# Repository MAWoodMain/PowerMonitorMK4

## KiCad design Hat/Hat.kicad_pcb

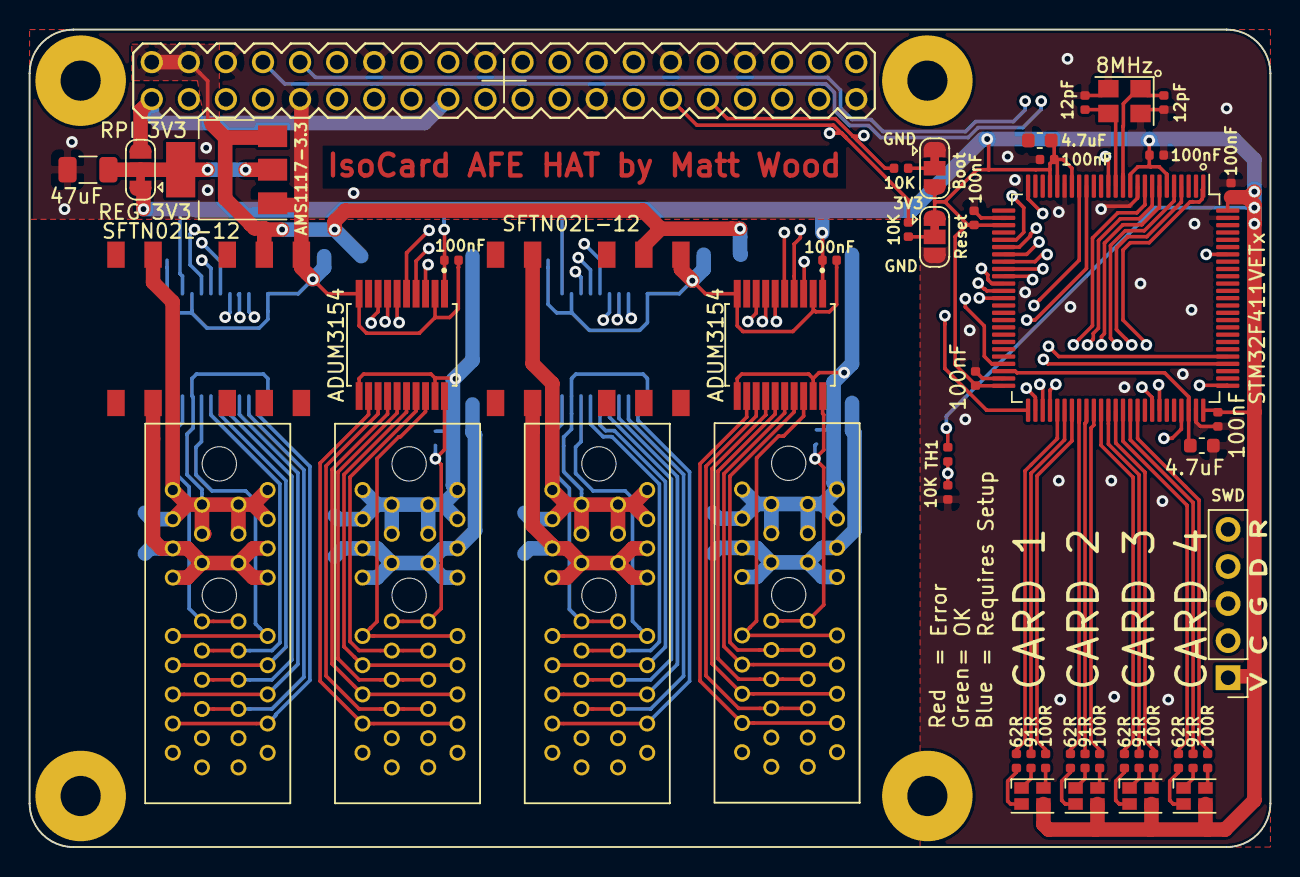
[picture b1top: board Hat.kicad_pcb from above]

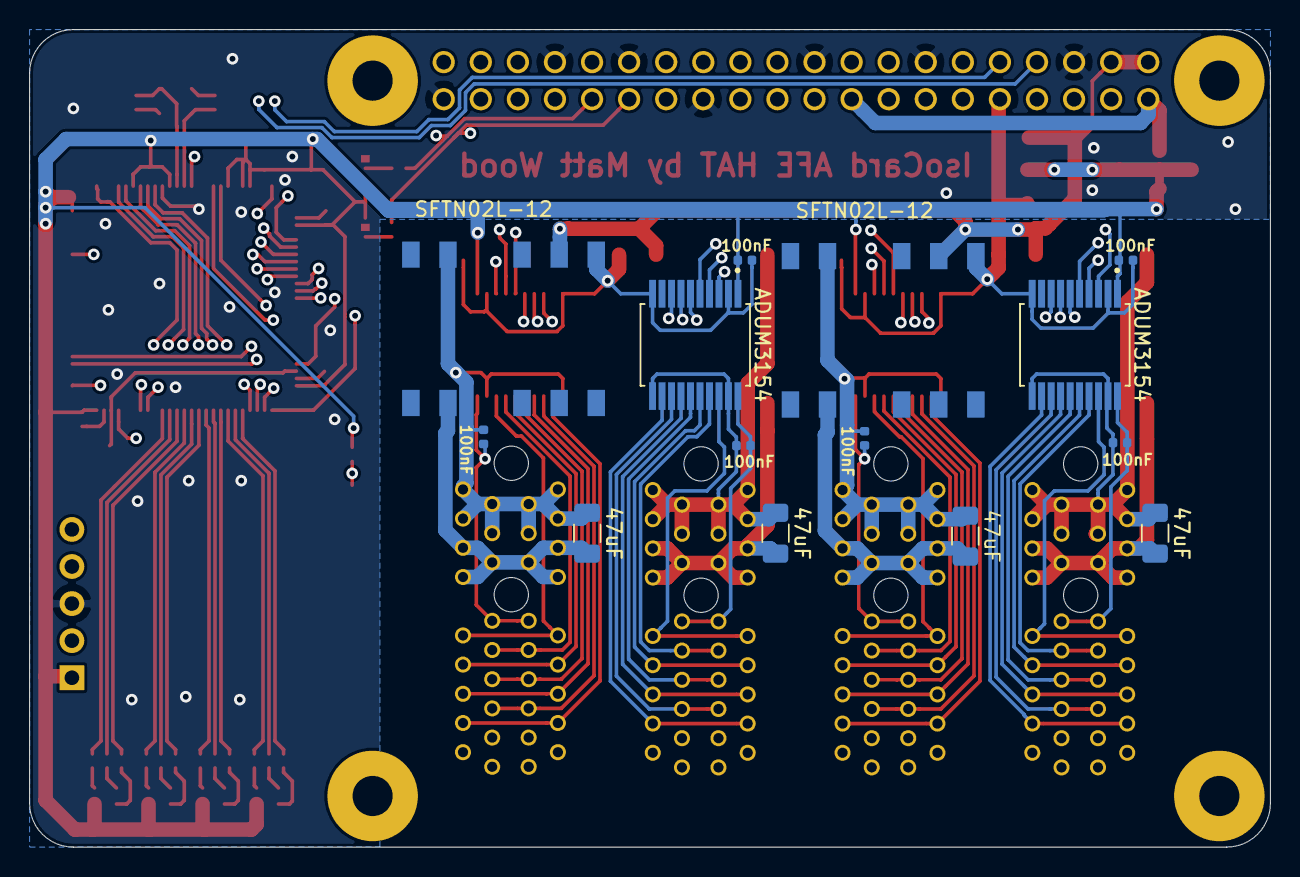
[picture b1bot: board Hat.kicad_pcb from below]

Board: 4 copper layers, 85.0 x 56.0 mm, 63 parts (14 on the bottom side), 105 nets.

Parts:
C1, C2: 4.7uF; C_0603_1608Metric
C3, C4, C5, C6, C7, C8, C11, C12, C13, C14, C15, C16, C17, C18: 100nF; C_0402_1005Metric
C9, C10: 12pF; C_0402_1005Metric
C19, C20, C21, C22, C23: 47uF; C_1206_3216Metric
CRD1, CRD2, CRD3, CRD4: AFE_Card_Interface; PCIE-036-02-X-D-TH
D1, D2, D3, D4: LED_RBAG; LED_Cree-PLCC4_2x2mm_CW
J1: Raspberry_Pi_2_3; RASPBERRY_PI_B+
J2: SWD; PinHeader_1x05_P2.54mm_Vertical
JP1: Reset; SolderJumper-3_P1.3mm_Bridged12_RoundedPad1.0x1.5mm
JP2: Boot; SolderJumper-3_P1.3mm_Bridged12_RoundedPad1.0x1.5mm
JP3: 3V3 SEL; SolderJumper-3_P1.3mm_Bridged12_RoundedPad1.0x1.5mm
PS1, PS2, PS3, PS4: SFTN02L-12; SFTN02
R1, R2: 10K; R_0402_SILK_VAL
R3, R4, R5, R6: 91R; R_0402_SILK_VAL
R7, R8, R9, R10: 62R; R_0402_SILK_VAL
R11, R12, R13, R14: 100R; R_0402_SILK_VAL
R15: 10K; R_0402_1005Metric
TH1: 10K; R_0402_1005Metric
U1, U2, U3, U4: ADUM3154; SOP65P780X200-20N
U5: STM32F411VETx; LQFP-100_14x14mm_P0.5mm
U6: AMS1117-3.3; SOT-223-3_TabPin2
Y1: 8MHz; Crystal_SMD_3225-4Pin_3.2x2.5mm

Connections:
+3.3VP: J1.1, J1.17, JP3.3
+3V3: C2.1, C3.1, C4.1, C5.1, C6.1, C7.1, C8.1, C11.1, C12.1, C13.1, C14.1, D1.3, D2.3, D3.3, D4.3, J2.1, JP1.1, JP2.3, JP3.1, TH1.1, U1.1, U2.1, U3.1, U4.1, U5.6, U5.11, U5.19, U5.21, U5.22, U5.28, U5.50, U5.75, U5.100
+5V: J1.2, J1.4, PS1.2, PS2.2, PS3.2, PS4.2, U6.3
/B1: D1.2, R11.1
/B1IO: R11.2, U5.57
/B2: D2.2, R12.1
/B2IO: R12.2, U5.60
/B3: D3.2, R13.1
/B3IO: R13.2, U5.63
/B4: D4.2, R14.1
/B4IO: R14.2, U5.66
/Board_Temp: R15.1, TH1.2, U5.25
/G1: D1.4, R7.1
/G1IO: R7.2, U5.55
/G2: D2.4, R8.1
/G2IO: R8.2, U5.58
/G3: D3.4, R9.1
/G3IO: R9.2, U5.61
/G4: D4.4, R10.1
/G4IO: R10.2, U5.64
/R1: D1.1, R3.1
/R1IO: R3.2, U5.56
/R2: D2.1, R4.1
/R2IO: R4.2, U5.59
/R3: D3.1, R5.1
/R3IO: R5.2, U5.62
/R4: D4.1, R6.1
/R4IO: R6.2, U5.65
/SPI1_MISO: U1.5, U5.31
/SPI1_MOSI: U1.4, U5.32
/SPI1_SCK: U1.3, U5.30
/SPI2_MISO: U2.5, U5.17
/SPI2_MOSI: U2.4, U5.18
/SPI2_SCK: U2.3, U5.47
/SPI3_MISO: U3.5, U5.79
/SPI3_MOSI: U3.4, U5.80
/SPI3_SCK: U3.3, U5.51
/SPI4_MISO: U4.5, U5.4
/SPI4_MOSI: U4.4, U5.5
/SPI4_SCK: U4.3, U5.1
/SSA1: U1.6, U5.33
/SSA2: U2.6, U5.38
/SSA3: U3.6, U5.52
/SSA4: U4.6, U5.7
/SSB1: U1.7, U5.34
/SSB2: U2.7, U5.37
/SSB3: U3.7, U5.53
/SSB4: U4.7, U5.8
/SSC1: U1.8, U5.35
/SSC2: U2.8, U5.36
/SSC3: U3.8, U5.54
/SSC4: U4.8, U5.9
/ST_BOOT0: J1.31, R2.2, U5.94
/ST_RST: J1.29, J2.5, R1.2, U5.14
/SWCLK: J2.2, U5.76
/SWDIO: J2.4, U5.72
/USART1_RX: J1.8, U5.69
/USART1_TX: J1.10, U5.68
/XTAL_IN: C9.1, U5.12, Y1.1
/XTAL_OUT: C10.1, U5.13, Y1.3
GND: C1.2, C2.2, C3.2, C4.2, C5.2, C6.2, C7.2, C8.2, C9.2, C10.2, C11.2, C12.2, C13.2, C14.2, C23.2, J1.6, J1.9, J1.14, J1.20, J1.25, J1.30, J1.34, J1.39, J2.3, JP1.3, JP2.1, PS1.1, PS2.1, PS3.1, PS4.1, R15.2, U1.2, U1.10, U2.2, U2.10, U3.2, U3.10, U4.2, U4.10, U5.10, U5.20, U5.27, U5.49, U5.74, U5.99, U6.1, Y1.2, Y1.4
unnamed: C1.1, U5.48, U5.73
unnamed: C15.1, C19.2, CRD1.A15, CRD1.A16, CRD1.A17, CRD1.A18, CRD1.B15, CRD1.B16, CRD1.B17, CRD1.B18, PS1.5, U1.11, U1.19
unnamed: C15.2, CRD1.A11, CRD1.B11, U1.20
unnamed: C16.1, C20.2, CRD2.A15, CRD2.A16, CRD2.A17, CRD2.A18, CRD2.B15, CRD2.B16, CRD2.B17, CRD2.B18, PS2.5, U2.11, U2.19
unnamed: C16.2, CRD2.A11, CRD2.B11, U2.20
unnamed: C17.1, C21.2, CRD3.A15, CRD3.A16, CRD3.A17, CRD3.A18, CRD3.B15, CRD3.B16, CRD3.B17, CRD3.B18, PS3.5, U3.11, U3.19
unnamed: C17.2, CRD3.A11, CRD3.B11, U3.20
unnamed: C18.1, C22.2, CRD4.A15, CRD4.A16, CRD4.A17, CRD4.A18, CRD4.B15, CRD4.B16, CRD4.B17, CRD4.B18, PS4.5, U4.11, U4.19
unnamed: C18.2, CRD4.A11, CRD4.B11, U4.20
unnamed: C19.1, CRD1.A12, CRD1.A13, CRD1.A14, CRD1.B12, CRD1.B13, CRD1.B14, PS1.8
unnamed: C20.1, CRD2.A12, CRD2.A13, CRD2.A14, CRD2.B12, CRD2.B13, CRD2.B14, PS2.8
unnamed: C21.1, CRD3.A12, CRD3.A13, CRD3.A14, CRD3.B12, CRD3.B13, CRD3.B14, PS3.8
unnamed: C22.1, CRD4.A12, CRD4.A13, CRD4.A14, CRD4.B12, CRD4.B13, CRD4.B14, PS4.8
unnamed: C23.1, JP3.2, U6.2
unnamed: CRD1.A4, CRD1.B4, U1.12
unnamed: CRD1.A5, CRD1.B5, U1.13
unnamed: CRD1.A6, CRD1.B6, U1.14
unnamed: CRD1.A7, CRD1.B7, U1.15
unnamed: CRD1.A8, CRD1.B8, U1.16
unnamed: CRD1.A9, CRD1.B9, U1.17
unnamed: CRD1.A10, CRD1.B10, U1.18
unnamed: CRD2.A4, CRD2.B4, U2.12
unnamed: CRD2.A5, CRD2.B5, U2.13
unnamed: CRD2.A6, CRD2.B6, U2.14
unnamed: CRD2.A7, CRD2.B7, U2.15
unnamed: CRD2.A8, CRD2.B8, U2.16
unnamed: CRD2.A9, CRD2.B9, U2.17
unnamed: CRD2.A10, CRD2.B10, U2.18
unnamed: CRD3.A4, CRD3.B4, U3.12
unnamed: CRD3.A5, CRD3.B5, U3.13
unnamed: CRD3.A6, CRD3.B6, U3.14
unnamed: CRD3.A7, CRD3.B7, U3.15
unnamed: CRD3.A8, CRD3.B8, U3.16
unnamed: CRD3.A9, CRD3.B9, U3.17
unnamed: CRD3.A10, CRD3.B10, U3.18
unnamed: CRD4.A4, CRD4.B4, U4.12
unnamed: CRD4.A5, CRD4.B5, U4.13
unnamed: CRD4.A6, CRD4.B6, U4.14
unnamed: CRD4.A7, CRD4.B7, U4.15
unnamed: CRD4.A8, CRD4.B8, U4.16
unnamed: CRD4.A9, CRD4.B9, U4.17
unnamed: CRD4.A10, CRD4.B10, U4.18
unnamed: JP1.2, R1.1
unnamed: JP2.2, R2.1

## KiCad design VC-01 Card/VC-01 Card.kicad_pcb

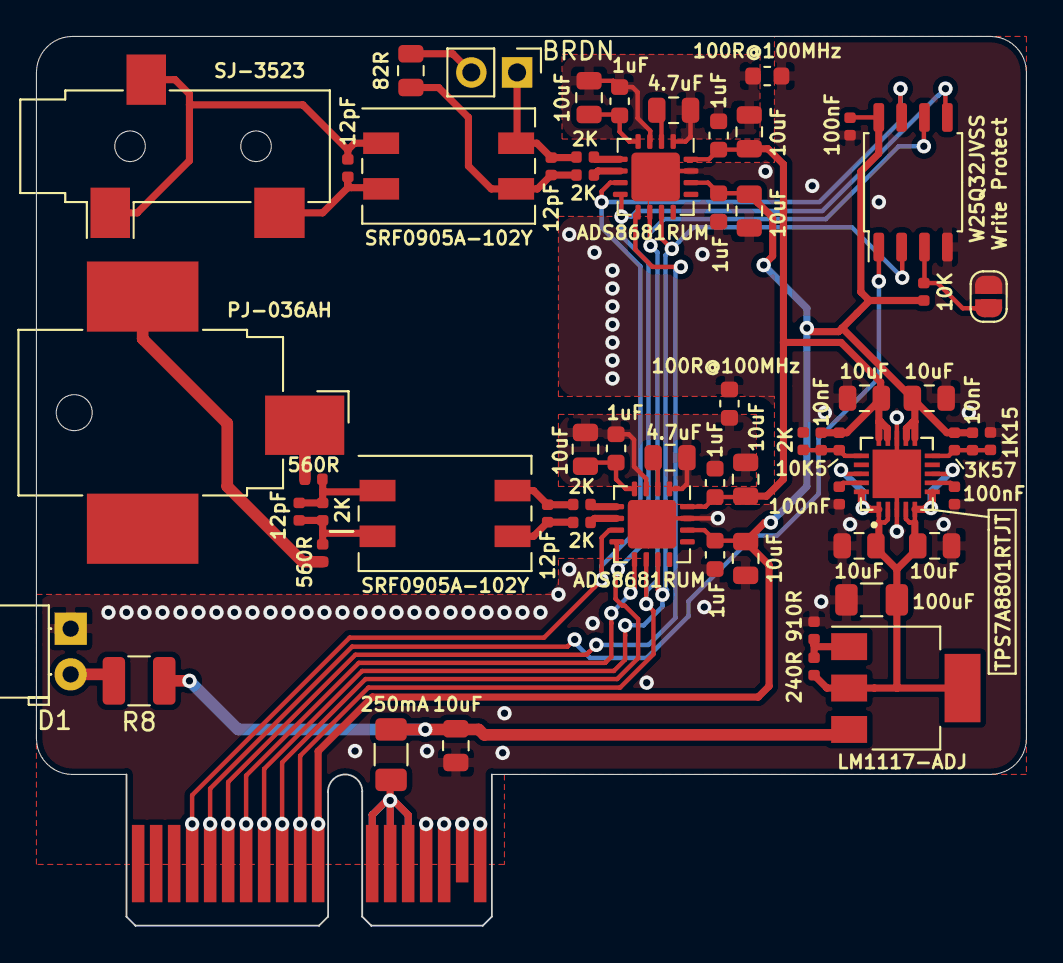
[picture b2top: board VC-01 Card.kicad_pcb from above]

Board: 2 copper layers, 55.0 x 49.4 mm, 61 parts (0 on the bottom side), 41 nets.

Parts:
C1, C2, C7, C8: 12pF; C_0402_1005Metric
C3, C4, C12, C13, C16, C17, C22, C23, C26, C27, C29: 10uF; C_0805_2012Metric
C5, C6, C9: 100nF; C_0402_1005Metric
C10, C11, C18, C19, C20, C21: 1uF; C_0603_1608Metric
C14, C15: 4.7uF; C_0805_2012Metric
C24, C25: 10nF; C_0402_1005Metric
C28: 100uF; C_1206_3216Metric
CRD1: AFE_Card_Interface; BUS_PCIexpress_x1
D1: LED; LED_D5.0mm_Horizontal_O1.27mm_Z3.0mm
F1: 250mA; Fuse_1206_3216Metric
FB1, FB2: 100R@100MHz; R_0603_1608Metric
FL1, FL2: SRF0905A-102Y; Filter_Bourns_SRF0905_6.0x9.2mm
J1: SJ-3523; Jack_3.5mm_CUI_SJ-3523-SMT_Horizontal
J2: PJ-036AH; BarrelJack_CUI_PJ-036AH-SMT_Horizontal
J3: BRDN; PinHeader_1x02_P2.54mm_Vertical
JP1: Write Protect; SolderJumper-2_P1.3mm_Open_RoundedPad1.0x1.5mm
R1: 82R; R_0805_2012Metric
R2, R3, R6, R11, R12, R13: 2K; R_0402_1005Metric
R4: 10K5; R_0402_1005Metric
R5: 3K57; R_0402_1005Metric
R7: 1K15; R_0402_1005Metric
R8: R; R_1210_3225Metric
R9, R10: 560R; R_0402_1005Metric
R14: 10K; R_0402_1005Metric
R15: 240R; R_0402_1005Metric
R16: 910R; R_0402_1005Metric
U1, U3: ADS8681RUM; QFN-16-1EP_4x4mm_P0.65mm_EP2.7x2.7mm
U2: TPS7A8801RTJT; QFN50P400X400X80-21N
U4: W25Q32JVSS; SOIC-8_5.23x5.23mm_P1.27mm
U5: LM1117-ADJ; SOT-223-3_TabPin2

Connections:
+3V3: C3.1, C9.2, C20.1, C21.1, C22.1, C23.1, C25.2, CRD1.A11, CRD1.B11, R5.1, R14.1, U1.14, U2.11, U2.12, U3.14, U4.8
+5V: C4.1, C10.1, C11.1, C12.1, C13.1, C24.2, R4.1, U1.16, U2.14, U2.15, U3.16
+12V: C29.1, F1.2, R8.1, U5.3
/SCLK: CRD1.A10, CRD1.B10, U1.10, U3.10, U4.6
/SI: CRD1.A9, CRD1.B9, U1.8, U3.8, U4.5
/SO: CRD1.A8, CRD1.B8, U1.11, U3.11, U4.2
/U1_GNDA: C11.2, C13.2, C15.2, C17.2, C19.2, FB1.1, U1.1, U1.3
/U3_GNDA: C10.2, C12.2, C14.2, C16.2, C18.2, FB2.1, U3.1, U3.3
/~CS_CURRENT: CRD1.A6, CRD1.B6, U1.9
/~CS_FLASH: CRD1.A5, CRD1.B5, U4.1
/~CS_VOLTAGE: CRD1.A7, CRD1.B7, U3.9
/~RST: CRD1.A4, CRD1.B4, U1.7, U3.7, U4.7
GND: C3.2, C4.2, C5.1, C6.1, C9.1, C20.2, C21.2, C22.2, C23.2, C26.2, C27.2, C28.2, C29.2, CRD1.A15, CRD1.A16, CRD1.A17, CRD1.A18, CRD1.B15, CRD1.B16, CRD1.B17, CRD1.B18, D1.1, FB1.2, FB2.2, JP1.2, R6.2, R7.2, R16.2, U1.15, U1.17, U2.3, U2.13, U2.21, U3.15, U3.17, U4.4
unnamed: C1.1, FL1.1, J1.R, J1.S
unnamed: C1.2, FL1.2, J1.T
unnamed: C2.1, FL1.4, J3.1, R2.2
unnamed: C2.2, FL1.3, R1.2, R3.2
unnamed: C5.2, U2.19
unnamed: C6.2, U2.7
unnamed: C7.1, FL2.1, R10.1, R11.1
unnamed: C7.2, FL2.2, R9.1, R11.2
unnamed: C8.1, FL2.4, R12.2
unnamed: C8.2, FL2.3, R13.2
unnamed: C14.1, U3.2
unnamed: C15.1, U1.2
unnamed: C16.1, C18.1, U3.4
unnamed: C17.1, C19.1, U1.4
unnamed: C24.1, R4.2, R6.1, U2.16
unnamed: C25.1, R5.2, R7.1, U2.10
unnamed: C26.1, C27.1, C28.1, R15.1, U2.1, U2.2, U2.4, U2.5, U2.6, U2.8, U2.18, U2.20, U5.2
unnamed: CRD1.A12, CRD1.A13, CRD1.A14, CRD1.B12, CRD1.B13, CRD1.B14, F1.1
unnamed: D1.2, R8.2
unnamed: J2.1, R10.2
unnamed: J2.2, R9.2
unnamed: J3.2, R1.1
unnamed: JP1.1, R14.2, U4.3
unnamed: R2.1, U1.5
unnamed: R3.1, U1.6
unnamed: R12.1, U3.5
unnamed: R13.1, U3.6
unnamed: R15.2, R16.1, U5.1

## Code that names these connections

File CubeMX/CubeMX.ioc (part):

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Mcu.Name=STM32F411V(C-E)Tx
Mcu.Package=LQFP100
Mcu.UserName=STM32F411VETx
PA1.GPIOParameters=GPIO_Label
PA1.GPIO_Label=Board_Temp
PA1.Signal=ADCx_IN1
PA10.Mode=Asynchronous
PA10.Signal=USART1_RX
PA5.Mode=Full_Duplex_Master
PA5.Signal=SPI1_SCK
PA6.Mode=Full_Duplex_Master
PA6.Signal=SPI1_MISO
PA7.Mode=Full_Duplex_Master
PA7.Signal=SPI1_MOSI
PA9.Mode=Asynchronous
PA9.Signal=USART1_TX
PB0.GPIOParameters=PinState,GPIO_PuPd,GPIO_Label
PB0.GPIO_Label=SSC1
PB0.GPIO_PuPd=GPIO_PULLUP
PB0.PinState=GPIO_PIN_SET
PB0.Signal=GPIO_Output
PB1.GPIOParameters=PinState,GPIO_PuPd,GPIO_Label,GPIO_ModeDefaultOutputPP
PB1.GPIO_Label=SSC2
PB1.GPIO_ModeDefaultOutputPP=GPIO_MODE_OUTPUT_PP
PB1.GPIO_PuPd=GPIO_PULLUP
PB1.PinState=GPIO_PIN_SET
PB1.Signal=GPIO_Output
PB10.Mode=Full_Duplex_Master
PB10.Signal=SPI2_SCK
PB12.Mode=Full_Duplex_Master
PB12.Signal=SPI3_SCK
PB13.GPIOParameters=PinState,GPIO_PuPd,GPIO_Label,GPIO_ModeDefaultOutputPP
PB13.GPIO_Label=SSA3
PB13.GPIO_ModeDefaultOutputPP=GPIO_MODE_OUTPUT_PP
PB13.GPIO_PuPd=GPIO_PULLUP
PB13.PinState=GPIO_PIN_SET
PB13.Signal=GPIO_Output
PB14.GPIOParameters=PinState,GPIO_PuPd,GPIO_Label,GPIO_ModeDefaultOutputPP
PB14.GPIO_Label=SSB3
PB14.GPIO_ModeDefaultOutputPP=GPIO_MODE_OUTPUT_PP
PB14.GPIO_PuPd=GPIO_PULLUP
PB14.PinState=GPIO_PIN_SET
PB14.Signal=GPIO_Output
PB15.GPIOParameters=PinState,GPIO_PuPd,GPIO_Label,GPIO_ModeDefaultOutputPP
PB15.GPIO_Label=SSC3
PB15.GPIO_ModeDefaultOutputPP=GPIO_MODE_OUTPUT_PP
PB15.GPIO_PuPd=GPIO_PULLUP
PB15.PinState=GPIO_PIN_SET
PB15.Signal=GPIO_Output
PB2.GPIOParameters=PinState,GPIO_PuPd,GPIO_Label,GPIO_ModeDefaultOutputPP
PB2.GPIO_Label=SSB2
PB2.GPIO_ModeDefaultOutputPP=GPIO_MODE_OUTPUT_PP
PB2.GPIO_PuPd=GPIO_PULLUP
PB2.PinState=GPIO_PIN_SET
PB2.Signal=GPIO_Output
PC11.Mode=Full_Duplex_Master
PC11.Signal=SPI3_MISO
PC12.Mode=Full_Duplex_Master
PC12.Signal=SPI3_MOSI
PC13-ANTI_TAMP.GPIOParameters=PinState,GPIO_PuPd,GPIO_Label,GPIO_ModeDefaultOutputPP
PC13-ANTI_TAMP.GPIO_Label=SSA4
PC13-ANTI_TAMP.GPIO_ModeDefaultOutputPP=GPIO_MODE_OUTPUT_PP
PC13-ANTI_TAMP.GPIO_PuPd=GPIO_PULLUP
PC13-ANTI_TAMP.PinState=GPIO_PIN_SET
PC13-ANTI_TAMP.Signal=GPIO_Output
PC14-OSC32_IN.GPIOParameters=PinState,GPIO_PuPd,GPIO_Label,GPIO_ModeDefaultOutputPP
PC14-OSC32_IN.GPIO_Label=SSB4
PC14-OSC32_IN.GPIO_ModeDefaultOutputPP=GPIO_MODE_OUTPUT_PP
PC14-OSC32_IN.GPIO_PuPd=GPIO_PULLUP
PC14-OSC32_IN.PinState=GPIO_PIN_SET
PC14-OSC32_IN.Signal=GPIO_Output
PC15-OSC32_OUT.GPIOParameters=PinState,GPIO_PuPd,GPIO_Label,GPIO_ModeDefaultOutputPP
PC15-OSC32_OUT.GPIO_Label=SSC4
PC15-OSC32_OUT.GPIO_ModeDefaultOutputPP=GPIO_MODE_OUTPUT_PP
PC15-OSC32_OUT.GPIO_PuPd=GPIO_PULLUP
PC15-OSC32_OUT.PinState=GPIO_PIN_SET
PC15-OSC32_OUT.Signal=GPIO_Output
PC2.Mode=Full_Duplex_Master
PC2.Signal=SPI2_MISO
PC3.Mode=Full_Duplex_Master
PC3.Signal=SPI2_MOSI
PC4.GPIOParameters=PinState,GPIO_PuPd,GPIO_Label,GPIO_ModeDefaultOutputPP
PC4.GPIO_Label=SSA1
PC4.GPIO_ModeDefaultOutputPP=GPIO_MODE_OUTPUT_PP
PC4.GPIO_PuPd=GPIO_PULLUP
PC4.PinState=GPIO_PIN_SET
PC4.Signal=GPIO_Output
PC5.GPIOParameters=PinState,GPIO_PuPd,GPIO_Label,GPIO_ModeDefaultOutputPP
PC5.GPIO_Label=SSB1
PC5.GPIO_ModeDefaultOutputPP=GPIO_MODE_OUTPUT_PP
PC5.GPIO_PuPd=GPIO_PULLUP
PC5.PinState=GPIO_PIN_SET
PC5.Signal=GPIO_Output
PC6.GPIOParameters=PinState,GPIO_Label,GPIO_ModeDefaultOutputPP
PC6.GPIO_Label=B3
PC6.GPIO_ModeDefaultOutputPP=GPIO_MODE_OUTPUT_OD
PC6.PinState=GPIO_PIN_SET
PC6.Signal=GPIO_Output
PC7.GPIOParameters=PinState,GPIO_Label,GPIO_ModeDefaultOutputPP
PC7.GPIO_Label=G4
PC7.GPIO_ModeDefaultOutputPP=GPIO_MODE_OUTPUT_OD
PC7.PinState=GPIO_PIN_SET
PC7.Signal=GPIO_Output
PC8.GPIOParameters=PinState,GPIO_Label,GPIO_ModeDefaultOutputPP
PC8.GPIO_Label=R4
PC8.GPIO_ModeDefaultOutputPP=GPIO_MODE_OUTPUT_OD
PC8.PinState=GPIO_PIN_SET
PC8.Signal=GPIO_Output
PC9.GPIOParameters=PinState,GPIO_Label,GPIO_ModeDefaultOutputPP
PC9.GPIO_Label=B4
PC9.GPIO_ModeDefaultOutputPP=GPIO_MODE_OUTPUT_OD
PC9.PinState=GPIO_PIN_SET
PC9.Signal=GPIO_Output
PD10.GPIOParameters=PinState,GPIO_Label,GPIO_ModeDefaultOutputPP
PD10.GPIO_Label=B1
PD10.GPIO_ModeDefaultOutputPP=GPIO_MODE_OUTPUT_OD
PD10.PinState=GPIO_PIN_SET
PD10.Signal=GPIO_Output
PD11.GPIOParameters=PinState,GPIO_Label,GPIO_ModeDefaultOutputPP
PD11.GPIO_Label=G2
PD11.GPIO_ModeDefaultOutputPP=GPIO_MODE_OUTPUT_OD
PD11.PinState=GPIO_PIN_SET
PD11.Signal=GPIO_Output
PD12.GPIOParameters=PinState,GPIO_Label,GPIO_ModeDefaultOutputPP
PD12.GPIO_Label=R2
PD12.GPIO_ModeDefaultOutputPP=GPIO_MODE_OUTPUT_OD
PD12.PinState=GPIO_PIN_SET
PD12.Signal=GPIO_Output
PD13.GPIOParameters=PinState,GPIO_Label,GPIO_ModeDefaultOutputPP
PD13.GPIO_Label=B2
PD13.GPIO_ModeDefaultOutputPP=GPIO_MODE_OUTPUT_OD
PD13.PinState=GPIO_PIN_SET
PD13.Signal=GPIO_Output
PD14.GPIOParameters=PinState,GPIO_Label,GPIO_ModeDefaultOutputPP
PD14.GPIO_Label=G3
PD14.GPIO_ModeDefaultOutputPP=GPIO_MODE_OUTPUT_OD
PD14.PinState=GPIO_PIN_SET
PD14.Signal=GPIO_Output
PD15.GPIOParameters=PinState,GPIO_Label,GPIO_ModeDefaultOutputPP
PD15.GPIO_Label=R3
PD15.GPIO_ModeDefaultOutputPP=GPIO_MODE_OUTPUT_OD
PD15.PinState=GPIO_PIN_SET
PD15.Signal=GPIO_Output
PD8.GPIOParameters=PinState,GPIO_Label,GPIO_ModeDefaultOutputPP
PD8.GPIO_Label=G1
PD8.GPIO_ModeDefaultOutputPP=GPIO_MODE_OUTPUT_OD
PD8.PinState=GPIO_PIN_SET
PD8.Signal=GPIO_Output
PD9.GPIOParameters=PinState,GPIO_Label,GPIO_ModeDefaultOutputPP
PD9.GPIO_Label=R1
PD9.GPIO_ModeDefaultOutputPP=GPIO_MODE_OUTPUT_OD
PD9.PinState=GPIO_PIN_SET
PD9.Signal=GPIO_Output
PE2.Mode=Full_Duplex_Master
PE2.Signal=SPI4_SCK
PE5.Mode=Full_Duplex_Master
PE5.Signal=SPI4_MISO
PE6.Mode=Full_Duplex_Master
PE6.Signal=SPI4_MOSI
PE7.GPIOParameters=GPIO_Speed,PinState,GPIO_PuPd,GPIO_Label,GPIO_ModeDefaultOutputPP
PE7.GPIO_Label=SSA2
PE7.GPIO_ModeDefaultOutputPP=GPIO_MODE_OUTPUT_PP
PE7.GPIO_PuPd=GPIO_PULLUP
PE7.GPIO_Speed=GPIO_SPEED_FREQ_LOW
PE7.PinState=GPIO_PIN_SET
PE7.Signal=GPIO_Output
PH0\ -\ OSC_IN.Mode=HSE-External-Oscillator
PH0\ -\ OSC_IN.Signal=RCC_OSC_IN
PH1\ -\ OSC_OUT.Mode=HSE-External-Oscillator
PH1\ -\ OSC_OUT.Signal=RCC_OSC_OUT
RCC.HSE_VALUE=25000000
RCC.SYSCLKFreq_VALUE=75000000
RCC.SYSCLKSource=RCC_SYSCLKSOURCE_PLLCLK
board=custom

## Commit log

2020-03-08 Completed PI Hat schematic and layout
2020-03-08 Added License
2020-03-08 Unmasked copper text
2020-03-09 Added suppliers & costed BOM
2020-03-12 Added git ignores for cache and bak files
2020-03-12 Initial schematic and provisional layout for voltage and current card added and added lib cache to gitignore
2020-03-12 Added VC-01 sheet title and exported schematic, gerbers and pdfs
2020-03-13 Added local regulator for rpi core reboot persistence
2020-03-13 Added burden resistor jumper
2020-03-13 Added value silkscreen to vc card
2020-03-14 Added BOM to VC-01 and tidied silkscreen, added thermistor to hat. Regenerated gerbers & PDFs
2020-03-14 Various BOM fixes
2020-03-14 Finalised and ordered
2020-03-15 Added base firmware project into vcs
2020-04-04 GOT BLINKING LIGHTS GOING ON THE FIRST OFF PCB (no mod wires :D)
2020-04-04 Successfully read the flash chip and identified
2020-04-05 Added ADC interface (read only atm)
2020-04-05 Added command parser for serial interface and preparing to implement serial comms
2020-04-05 Implemented uart receive system, working
2020-04-05 Added read raw command, working
2020-04-10 Transitioned fully to a printf alternative library, and improved the serial interface command handling
2020-04-10 Safety commit, does not work, implemented a proper card abstraction and brought in SPIFFS, modified it to allow for the card structure.
2020-04-11 Fixed spiffs, working on hardfault issue on OS delay
2020-04-11 Added freertos overflow detection and added handler indication for overflow and hardfault
2020-04-11 Switched main task to static allocation and enabled freertos FPU support
2020-04-11 Implemented filesystem operations, tested & working. Added CRC module
2020-04-11 Added basic device config system
2020-04-11 Added card detection on all 4 slots
2020-04-11 Added realtime card detection and associated unsolicited messages
2020-04-12 Increased core clock up to 100MHz and increased uart clock to 460.8KHz
2020-04-18 Switched to one thread per card rtos system
2020-04-18 Restructured folders to separate cards, channels and management modules and added idle time measurement code
2020-04-18 Moved putchar into serial interface
2020-04-18 Added initial service files to repo
2020-04-18 Bump lodash.template from 4.4.0 to 4.5.0 in /Service/frontend
    Bumps [lodash.template](https://github.com/lodash/lodash) from 4.4.0 to 4.5.0.
    - [Release notes](https://github.com/lodash/lodash/releases)
    - [Commits](https://github.com/lodash/lodash/compare/4.4.0...4.5.0)
2020-04-18 Bump lodash from 4.17.10 to 4.17.15 in /Service/frontend
    Bumps [lodash](https://github.com/lodash/lodash) from 4.17.10 to 4.17.15.
    - [Release notes](https://github.com/lodash/lodash/releases)
    - [Commits](https://github.com/lodash/lodash/compare/4.17.10...4.17.15)
2020-04-18 Bump mixin-deep from 1.3.1 to 1.3.2 in /Service/frontend
    Bumps [mixin-deep](https://github.com/jonschlinkert/mixin-deep) from 1.3.1 to 1.3.2.
    - [Release notes](https://github.com/jonschlinkert/mixin-deep/releases)
    - [Commits](https://github.com/jonschlinkert/mixin-deep/compare/1.3.1...1.3.2)
2020-04-18 Bump handlebars from 4.0.12 to 4.7.6 in /Service/frontend
    Bumps [handlebars](https://github.com/wycats/handlebars.js) from 4.0.12 to 4.7.6.
    - [Release notes](https://github.com/wycats/handlebars.js/releases)
    - [Changelog](https://github.com/handlebars-lang/handlebars.js/blob/master/release-notes.md)
    - [Commits](https://github.com/wycats/handlebars.js/compare/v4.0.12...v4.7.6)
2020-04-19 Fixed for linux service deployment
2020-04-19 Updated front end deps
2020-04-19 Bump mongoose from 5.4.5 to 5.7.5 in /Service/backend
    Bumps [mongoose](https://github.com/Automattic/mongoose) from 5.4.5 to 5.7.5.
    - [Release notes](https://github.com/Automattic/mongoose/releases)
    - [Changelog](https://github.com/Automattic/mongoose/blob/master/History.md)
    - [Commits](https://github.com/Automattic/mongoose/compare/5.4.5...5.7.5)
2020-04-19 Bump lodash from 4.17.11 to 4.17.15 in /Service/backend
    Bumps [lodash](https://github.com/lodash/lodash) from 4.17.11 to 4.17.15.
    - [Release notes](https://github.com/lodash/lodash/releases)
    - [Commits](https://github.com/lodash/lodash/compare/4.17.11...4.17.15)
2020-04-19 Updated backend deps
2020-04-19 Bump mixin-deep from 1.3.1 to 1.3.2 in /Service/backend
    Bumps [mixin-deep](https://github.com/jonschlinkert/mixin-deep) from 1.3.1 to 1.3.2.
    - [Release notes](https://github.com/jonschlinkert/mixin-deep/releases)
    - [Commits](https://github.com/jonschlinkert/mixin-deep/compare/1.3.1...1.3.2)
2020-04-19 Initialisation tidyup
2020-06-08 Bump websocket-extensions from 0.1.3 to 0.1.4 in /Service/frontend
    Bumps [websocket-extensions](https://github.com/faye/websocket-extensions-node) from 0.1.3 to 0.1.4.
    - [Release notes](https://github.com/faye/websocket-extensions-node/releases)
    - [Changelog](https://github.com/faye/websocket-extensions-node/blob/master/CHANGELOG.md)
    - [Commits](https://github.com/faye/websocket-extensions-node/compare/0.1.3...0.1.4)
2020-07-20 Bump lodash from 4.17.15 to 4.17.19 in /Service/frontend
    Bumps [lodash](https://github.com/lodash/lodash) from 4.17.15 to 4.17.19.
    - [Release notes](https://github.com/lodash/lodash/releases)
    - [Commits](https://github.com/lodash/lodash/compare/4.17.15...4.17.19)
2020-07-20 Bump lodash from 4.17.15 to 4.17.19 in /Service
    Bumps [lodash](https://github.com/lodash/lodash) from 4.17.15 to 4.17.19.
    - [Release notes](https://github.com/lodash/lodash/releases)
    - [Commits](https://github.com/lodash/lodash/compare/4.17.15...4.17.19)
2020-07-20 Bump lodash from 4.17.11 to 4.17.19 in /Service/backend
    Bumps [lodash](https://github.com/lodash/lodash) from 4.17.11 to 4.17.19.
    - [Release notes](https://github.com/lodash/lodash/releases)
    - [Commits](https://github.com/lodash/lodash/compare/4.17.11...4.17.19)
2020-08-01 Bump elliptic from 6.5.2 to 6.5.3 in /Service/frontend
    Bumps [elliptic](https://github.com/indutny/elliptic) from 6.5.2 to 6.5.3.
    - [Release notes](https://github.com/indutny/elliptic/releases)
    - [Commits](https://github.com/indutny/elliptic/compare/v6.5.2...v6.5.3)
2020-09-02 Bump bl from 2.2.0 to 2.2.1 in /Service/backend
    Bumps [bl](https://github.com/rvagg/bl) from 2.2.0 to 2.2.1.
    - [Release notes](https://github.com/rvagg/bl/releases)
    - [Commits](https://github.com/rvagg/bl/compare/v2.2.0...v2.2.1)
2020-09-11 Bump http-proxy from 1.18.0 to 1.18.1 in /Service/frontend
    Bumps [http-proxy](https://github.com/http-party/node-http-proxy) from 1.18.0 to 1.18.1.
    - [Release notes](https://github.com/http-party/node-http-proxy/releases)
    - [Changelog](https://github.com/http-party/node-http-proxy/blob/master/CHANGELOG.md)
    - [Commits](https://github.com/http-party/node-http-proxy/compare/1.18.0...1.18.1)
2020-11-01 Added LED test on boot
2020-11-01 Added version number into flash in a fixed location
2020-11-01 Added proper URC printing of card data and locked timing against tick rate
